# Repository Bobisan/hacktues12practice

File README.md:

# hacktues12practice
This is a project, which we will use to prepare ourselves for Hack Tues 12

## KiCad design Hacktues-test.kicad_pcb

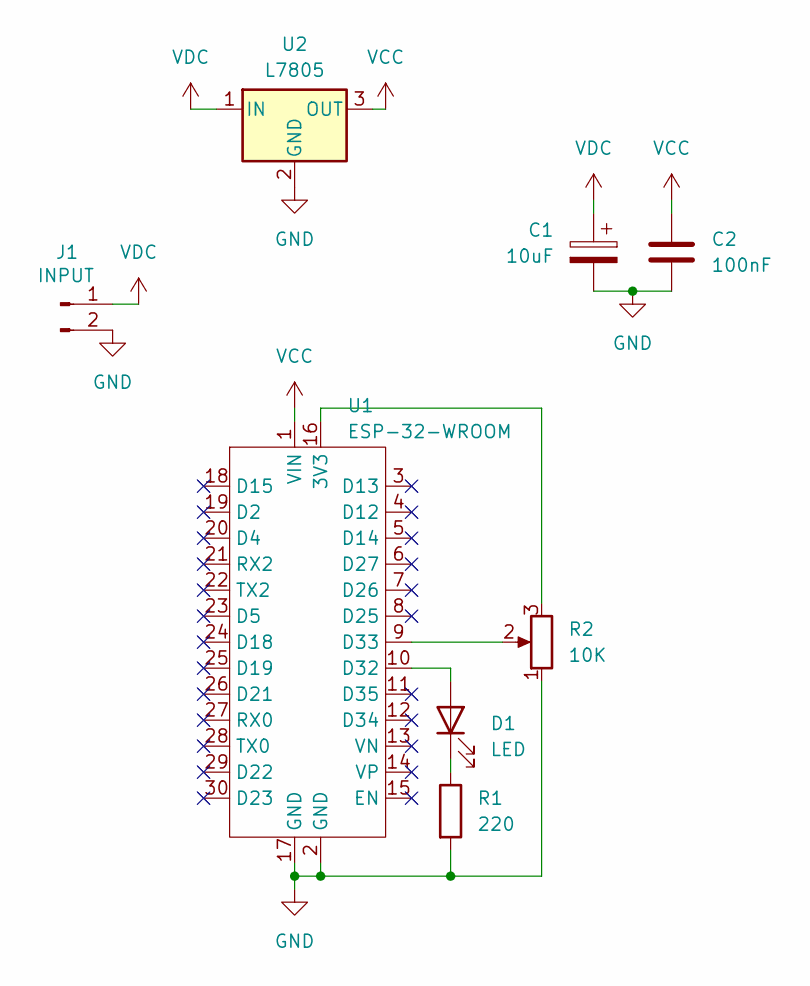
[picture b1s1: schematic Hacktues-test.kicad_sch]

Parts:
C1: 10uF; CP_Radial_D5.0mm_P2.50mm
C2: 100nF; C_Disc_D5.0mm_W2.5mm_P2.50mm
D1: LED; LED_D5.0mm
J1: INPUT; PinHeader_1x02_P2.54mm_Vertical
R1: 220; R_Axial_DIN0207_L6.3mm_D2.5mm_P10.16mm_Horizontal
R2: 10K; Potentiometer_Piher_T-16H_Single_Horizontal
U1: ESP-32-WROOM; ESP-32
U2: L7805; TO-220-3_Vertical

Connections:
GND: C1.2, C2.2, J1.2, R1.2, R2.1, U1.2 (GND), U1.17 (GND), U2.2 (GND)
unnamed: D1.2 (A), U1.10 (D32)
unnamed: D1.1 (K), R1.1
unnamed: R2.3, U1.16 (3V3)
unnamed: R2.2, U1.9 (D33)
VCC: C2.1, U1.1 (VIN), U2.3 (OUT)
VDC: C1.1, J1.1, U2.1 (IN)

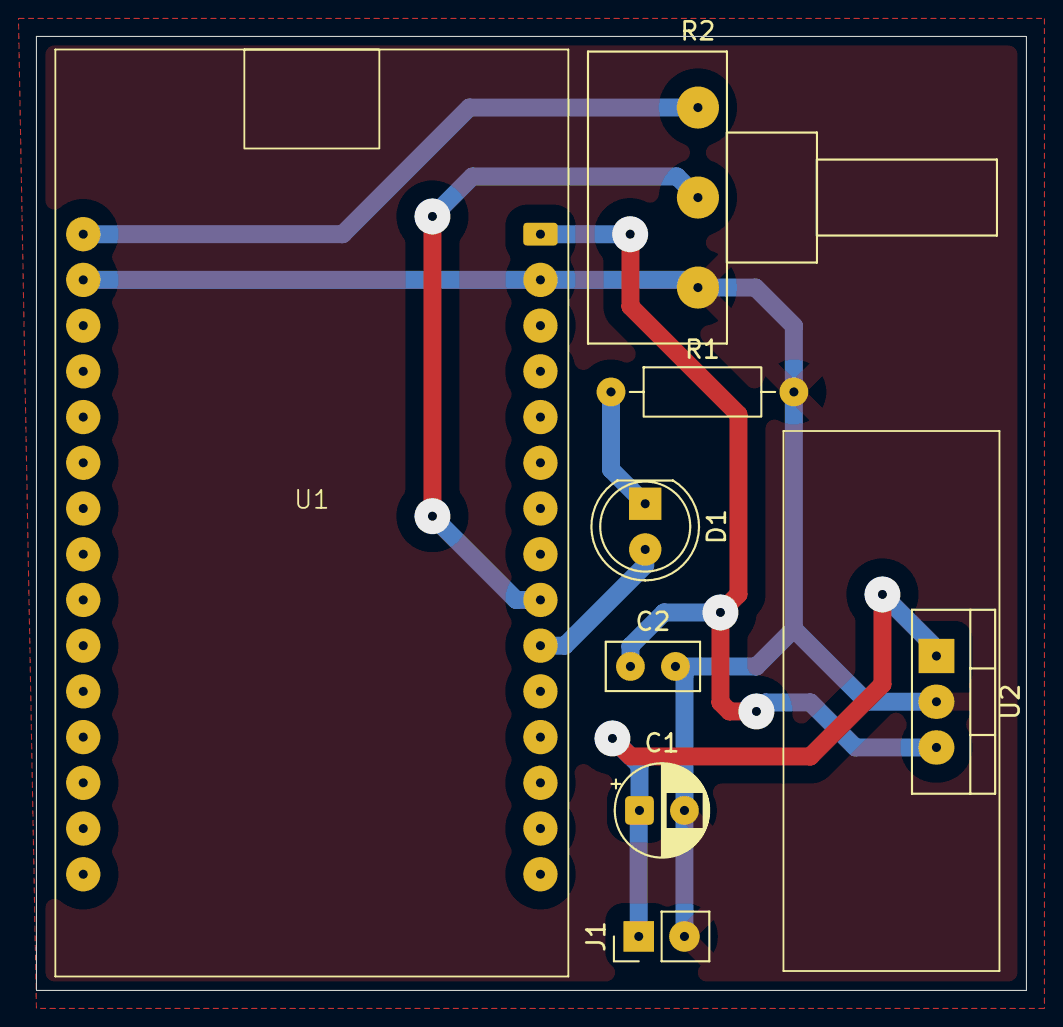
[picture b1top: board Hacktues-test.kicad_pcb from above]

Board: 2 copper layers, 55.0 x 53.0 mm, 8 parts (0 on the bottom side), 7 nets.

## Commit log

2026-03-10 Installed basic WebApp Template
2026-03-10 Added some buttons and pages for learning
2026-03-10 please commit
2026-03-10 Revert "please commit"
    This reverts commit c0cfc7474e6523a925d3ddd511e2e3ffff663fa1.
2026-03-10 removed tutorial site
2026-03-10 adding basic site to work on
2026-03-10 added react packages
2026-03-10 az bqh ne beshe chata
2026-03-10 test github
2026-03-10 HardaweV1
2026-03-10 added dtos and entities
2026-03-10 added services
2026-03-10 Found&Fixed-Error
2026-03-10 HardwareV1.1-Fixed
2026-03-10 adding baitotkjkghwrhknlekeqtpopkoetjowp
2026-03-10 synced up front end and backend
2026-03-10 I CENTERED
2026-03-10 Finalized all my testing. Database connection works.
2026-03-10 testint the mqtt brocker with siulating led and pot and it is successfull
2026-03-10 communication between fronend and backend is done and communication between backend and MariaDB established succesfully
2026-03-10 Added pot value receiving script that puts data into the database and a led frequency sending script
2026-03-10 i made it prettygit add . ':!.vs/'!!
2026-03-10 Removed files, useless to this branch
2026-03-10 nothing should happen
2026-03-11 fixed a problem with the index page with the divs
2026-03-11 cleaned up commentars
2026-03-11 added code for python script execution need to copy the files and give correct arguments
